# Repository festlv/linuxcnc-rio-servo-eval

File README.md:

# LinuxCNC-RIO evaluation/prototype board

This repository contains a quick&dirty board to evaluate feasibility of using [LinuxCNC-RIO](https://github.com/multigcs/LinuxCNC-RIO) for analog servo motor control.
The board is designed as an addon for [Colorlight i5](https://tomverbeure.github.io/2021/01/22/The-Colorlight-i5-as-FPGA-development-board.html) development board. 

Design contains:
* +/-10V analog output (from pwmdir input) + 24V enable output
* differential step/dir + single ended 24V enable output
* differential encoder input on DB9 connector (RS422) with index pulse. Pinout for Ditron DC10 linear scale.
* 4 single ended 24V inputs (limit switches, EStop)
* +24V input, +5V, +/- 15V outputs for development board and analog output.

__N.B.__: There is no isolation present on the board, it relies on the Ethernet isolation alone!

## Current state

The design is not verified in real hardware yet, proceed with caution. Some aspects of the design were simulated in LTSpice, see `ltspice/`

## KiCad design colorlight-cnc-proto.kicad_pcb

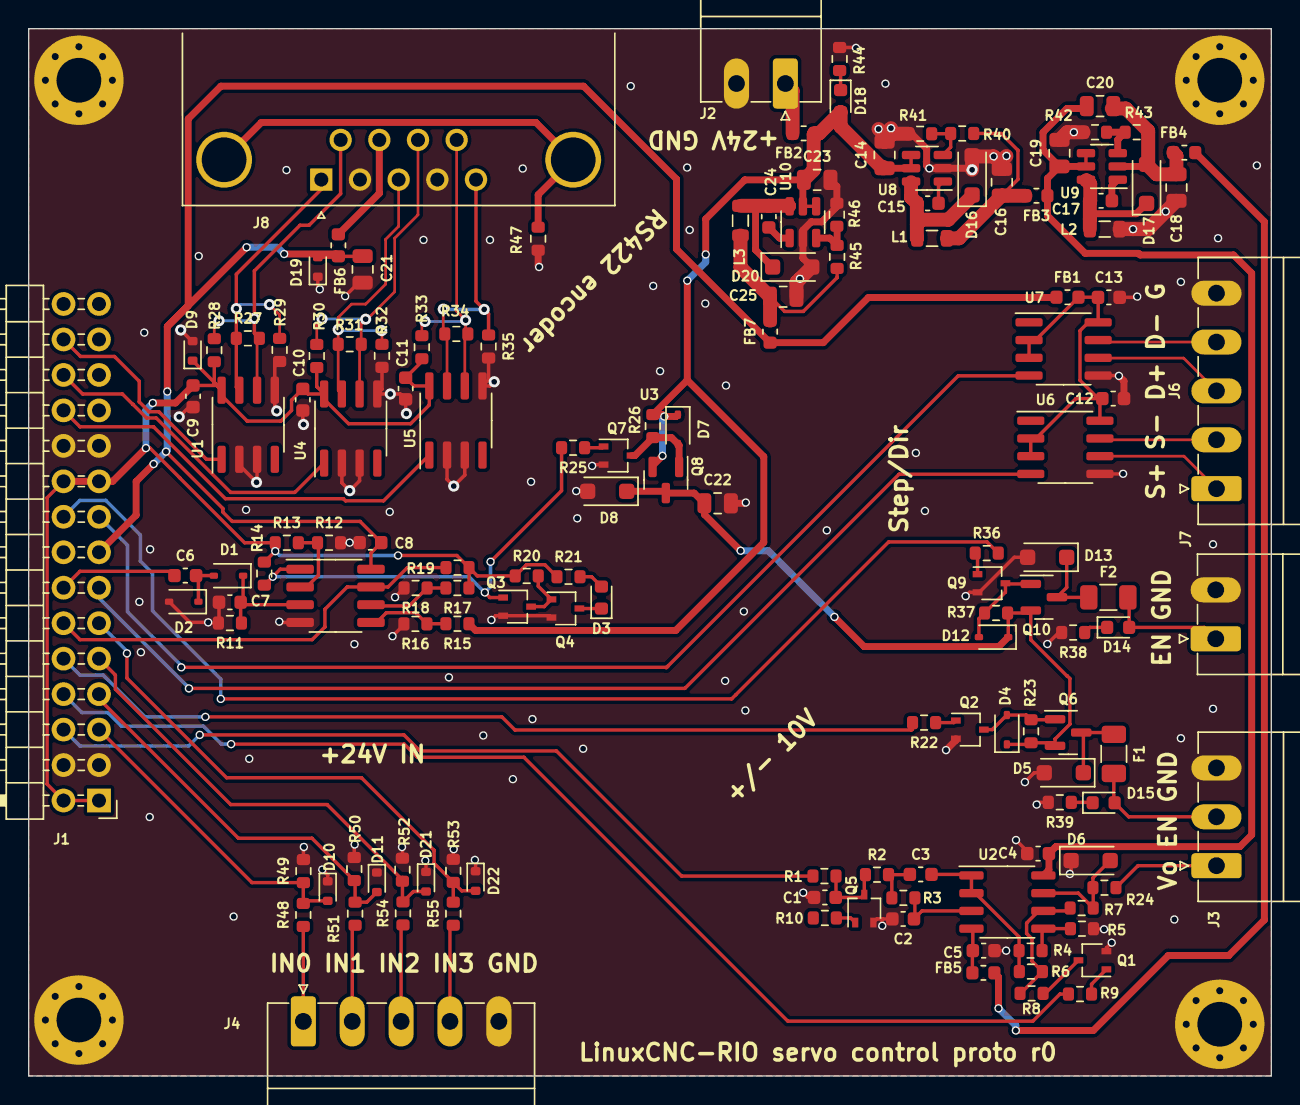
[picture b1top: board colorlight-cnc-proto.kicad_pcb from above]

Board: 2 copper layers, 89.0 x 75.0 mm, 145 parts (0 on the bottom side), 86 nets.

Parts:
C1: 3.3nF; C_0603_1608Metric
C2: 220pF; C_0603_1608Metric
C3: 680pF; C_0603_1608Metric
C4, C5, C6, C8, C9, C10, C11, C12, C13, C15, C17, C24: 0.1uF; C_0603_1608Metric
C7: 1uF; C_0603_1608Metric
C14, C16, C18, C19, C20, C21, C22, C23, C25: 10uF; C_0805_2012Metric
D1, D2: BAT54WS; D_SOD-323
D3, D14, D15: LED_RED; LED_0603_1608Metric
D4, D7, D12: BZT52C10S; D_SOD-323
D5, D8, D13: SMF24A; D_SOD-123F
D6: SMF10CA; D_SOD-123F
D9, D10, D11, D21, D22: BSD5C031V; D_SOD-523
D16, D17, D20: DSS34; D_SOD-123F
D18: LED_GREEN; LED_0603_1608Metric
D19: PESD5V0S1BBN; D_SOD-523
F1, F2: BSMD1206-100-24V; Fuse_1206_3216Metric
FB1, FB2, FB3, FB4, FB5, FB6, FB7: FB_100R_3A; L_0603_1608Metric
H1, H2, H3, H4: MH_3.2mm; MountingHole_3.2mm_M3_Pad_Via
J1: Conn_02x15_Odd_Even; PinHeader_2x15_P2.54mm_Horizontal
J2, J7: TERM-BLK-2H; PhoenixContact_MC_1,5_2-G-3.5_1x02_P3.50mm_Horizontal
J3: TERM-BLK-3H; PhoenixContact_MC_1,5_3-G-3.5_1x03_P3.50mm_Horizontal
J4, J6: TERM-BLK-5H; PhoenixContact_MC_1,5_5-G-3.5_1x05_P3.50mm_Horizontal
J8: DB9_Receptacle; DSUB-9_Female_Horizontal_P2.77x2.84mm_EdgePinOffset7.70mm_H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
L1, L2, L3: MLP2012S4R7MT0S1; L_0805_2012Metric
Q1, Q2, Q3, Q4, Q5, Q7, Q9: BSS138W; SOT-323_SC-70
Q6, Q8, Q10: AO3401A; SOT-23
R1, R4, R5, R6, R9, R10, R14, R15, R17, R18, R19, R20, R22, R23, R25, R26, R36, R37, R38, R39, R44, R48, R49, R50, R51, R52, R53, R54, R55: 10K; R_0603_1608Metric
R2: 150K; R_0603_1608Metric
R3, R11, R13: 47K; R_0603_1608Metric
R7: 70K; R_0603_1608Metric
R8: 5.83K; R_0603_1608Metric
R12: 100K; R_0603_1608Metric
R16, R21, R28, R29, R30, R32, R33, R35: 1K; R_0603_1608Metric
R24: 10R; R_0603_1608Metric
R27, R31, R34: 120R; R_0603_1608Metric
R40, R42: 510K; R_0603_1608Metric
R41, R43: 30K; R_0603_1608Metric
R45: 82K; R_0603_1608Metric
R46: 16K; R_0603_1608Metric
R47: 0R; R_0603_1608Metric
U1, U4, U5, U6, U7: CS48505S; SOIC-8_3.9x4.9mm_P1.27mm
U2: LM358DT; SO-8_3.9x4.9mm_P1.27mm
U3: LM2903; SOP-8_3.76x4.96mm_P1.27mm
U8, U9, U10: LGS5145; SOT-23-6

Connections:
+3V3: C9.1, C10.1, C11.1, D9.1 (A1), J1.1, J1.2, J1.19, J1.20, R13.1, R14.1, R17.1, R19.1, R20.1, R21.1, R28.1, R30.1, R33.1, U1.8 (VCC), U4.8 (VCC), U5.8 (VCC)
+5V: C8.1, C21.1, D19.2 (A2), FB1.1, FB6.1, FB7.1, J1.15, U3.8 (V+)
+15V: C4.1, C19.1, C20.1, FB3.1, U2.8 (V+), U9.4 (EN), U9.5 (IN)
+24V: C14.1, C23.1, D7.1 (K), D18.2 (A), FB2.2, Q8.2 (S), R15.1, R26.1, U8.4 (EN), U8.5 (IN), U10.4 (EN), U10.5 (IN)
+24V_WD: C22.1, D4.1 (K), D8.1 (A1), D12.1 (K), Q6.2 (S), Q8.3 (D), Q10.2 (S), R23.1, R37.1
-15V: FB4.2, FB5.2
/Analog output/DIR_IN: J1.8, R9.2
/Analog output/EN: J1.10, R22.2
/Analog output/EN_OUT: D15.2 (A), F1.2, J3.2
/Analog output/OUT: J3.1, R24.2
/Analog output/PWM_IN: J1.6, R1.1
/IO/INP0: D10.2 (A2), J1.5, R48.2, R49.1
/IO/INP1: D11.2 (A2), J1.7, R50.1, R51.2
/IO/INP2: D21.2 (A2), J1.9, R52.1, R54.2
/IO/INP3: D22.2 (A2), J1.11, R53.1, R55.2
/Quad encoder/A: J1.28, U1.1 (RO)
/Quad encoder/A_IN_N: J8.1, R27.1, R29.1, U1.7 (B)
/Quad encoder/A_IN_P: J8.6, R27.2, R28.2, U1.6 (A)
/Quad encoder/B: J1.26, U4.1 (RO)
/Quad encoder/B_IN_N: J8.3, R31.2, R32.1, U4.7 (B)
/Quad encoder/B_IN_P: J8.8, R30.2, R31.1, U4.6 (A)
/Quad encoder/Z: J1.24, U5.1 (RO)
/Quad encoder/Z_IN_N: J8.5, R34.2, R35.1, U5.7 (B)
/Quad encoder/Z_IN_P: J8.9, R33.2, R34.1, U5.6 (A)
/SD_EN: J1.18, R36.2
/Step Dir/DIR: J1.17, U7.4 (DI)
/Step Dir/DIR_OUT_N: J6.4, U7.7 (B)
/Step Dir/DIR_OUT_P: J6.3, U7.6 (A)
/Step Dir/EN_OUT: D14.2 (A), F2.2, J7.1
/Step Dir/STEP: J1.13, U6.4 (DI)
/Step Dir/STEP_OUT_N: J6.2, U6.7 (B)
/Step Dir/STEP_OUT_P: J6.1, U6.6 (A)
/Watchdog/24V_OK: J1.12, R19.2, U3.7
/Watchdog/PWM_IN: C6.1, J1.14
GND: C1.2, C2.2, C4.2, C5.2, C7.2, C8.2, C9.2, C10.2, C11.2, C12.2, C13.2, C14.2, C16.2, C18.1, C19.2, C21.2, C22.2, C23.2, C25.2, D2.2 (A), D5.2 (A2), D6.1 (A1), D8.2 (A2), D9.2 (A2), D10.1 (A1), D11.1 (A1), D13.2 (A2), D16.2 (A), D19.1 (A1), D20.2 (A), D21.1 (A1), D22.1 (A1), H1.1, H2.1, H3.1, H4.1, J1.3, J1.4, J1.21, J1.22, J2.2, J3.3, J4.5, J6.5, J7.2, J8.2, J8.4, L2.2, Q1.2 (S), Q2.2 (S), Q3.2 (S), Q4.2 (S), Q5.2 (S), Q7.2 (S), Q9.2 (S), R5.1, R11.2, R12.2, R16.2, R18.2, R29.2, R32.2, R35.2, R38.2, R39.2, R41.2, R42.1, R44.2, R46.2, R47.2, R49.2, R50.2, R52.2, R53.2, U1.2 (~RE), U1.3 (DE), U1.5 (GND), U3.4 (V-), U4.2 (~RE), U4.3 (DE), U4.5 (GND), U5.2 (~RE), U5.3 (DE), U5.5 (GND), U6.5 (GND), U7.5 (GND), U8.2 (GND), U10.2 (GND)
unnamed: C3.1, R2.2, R3.1
unnamed: C16.1, FB3.2, L1.2, R40.1
unnamed: C25.1, FB7.2, L3.2, R45.1
unnamed: C6.2, D1.2 (A), D2.1 (K)
unnamed: C7.1, D1.1 (K), R11.1, U3.3 (+)
unnamed: D3.2 (A), R21.2
unnamed: D3.1 (K), Q4.3 (D)
unnamed: D4.2 (A), Q2.3 (D), Q6.1 (G), R23.2
unnamed: D5.1 (A1), F1.1, Q6.3 (D)
unnamed: D6.2 (A2), R7.1, R24.1, U2.7
unnamed: D7.2 (A), Q7.3 (D), Q8.1 (G), R26.2
unnamed: D12.2 (A), Q9.3 (D), Q10.1 (G), R37.2
unnamed: D13.1 (A1), F2.1, Q10.3 (D)
unnamed: D14.1 (K), R38.1
unnamed: D15.1 (K), R39.1
unnamed: C15.2, D16.1 (K), L1.1, U8.6 (SW)
unnamed: C18.2, C20.2, D17.2 (A), FB4.1, R43.2, U9.2 (GND)
unnamed: C17.2, D17.1 (K), L2.1, U9.6 (SW)
unnamed: D18.1 (K), R44.1
unnamed: C24.2, D20.1 (K), L3.1, U10.6 (SW)
unnamed: FB6.2, J8.7
unnamed: FB2.1, J2.1
unnamed: J4.1, R48.1
unnamed: J4.2, R51.1
unnamed: J4.3, R54.1
unnamed: J4.4, R55.1
unnamed: J8.0 (PAD), R47.1
unnamed: Q1.3 (D), R8.1
unnamed: Q1.1 (G), R9.1
unnamed: Q2.1 (G), R22.1
unnamed: C1.1, Q5.3 (D), R1.2, R2.1
unnamed: Q5.1 (G), R10.1
unnamed: Q7.1 (G), R25.1
unnamed: Q9.1 (G), R36.1
unnamed: C2.1, R3.2, U2.3 (+)
unnamed: C3.2, R4.1, R6.2, U2.1, U2.2 (-)
unnamed: R4.2, R5.2, U2.5 (+)
unnamed: R6.1, R7.2, R8.2, U2.6 (-)
unnamed: C5.1, FB5.1, U2.4 (V-)
unnamed: R12.1, R13.2, U3.2 (-)
unnamed: R15.2, R16.1, U3.5 (+)
unnamed: R17.2, R18.1, U3.6 (-)
unnamed: C12.1, C13.1, FB1.2, U6.2 (~RE), U6.3 (DE), U6.8 (VCC), U7.2 (~RE), U7.3 (DE), U7.8 (VCC)
unnamed: C15.1, U8.1 (BS)
unnamed: R40.2, R41.1, U8.3 (FB)
unnamed: C17.1, U9.1 (BS)
unnamed: R42.2, R43.1, U9.3 (FB)
unnamed: C24.1, U10.1 (BS)
unnamed: R45.2, R46.1, U10.3 (FB)
WATCHDOG: Q3.1 (G), R14.2, R25.2, U3.1
WATCHDOG_INV: Q3.3 (D), Q4.1 (G), R20.2

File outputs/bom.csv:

"Source:","/home/reinis/personal/cnc/colorlight-cnc-proto/colorlight-cnc-proto.kicad_sch"
"Date:","Thu 07 Sep 2023 10:59:34 AM EEST"
"Tool:","Eeschema 7.0.7"
"Generator:","/usr/share/kicad/plugins/bom_csv_grouped_by_value.py"
"Component Count:","141"

"Collated Components:"

"Item","Qty","Reference(s)","Value","LibPart","Footprint","Datasheet","DNP","LCSC#","MPN","Manufacturer"
"1","1","C1","3.3nF","Device:C_Small","Capacitor_SMD:C_0603_1608Metric","~","","","",""
"2","1","C2","220pF","Device:C_Small","Capacitor_SMD:C_0603_1608Metric","~","","","",""
"3","1","C3","680pF","Device:C_Small","Capacitor_SMD:C_0603_1608Metric","~","","","",""
"4","12","C4, C5, C6, C8, C9, C10, C11, C12, C13, C15, C17, C24","0.1uF","Device:C_Small","Capacitor_SMD:C_0603_1608Metric","~","","","",""
"5","1","C7","1uF","Device:C_Small","Capacitor_SMD:C_0603_1608Metric","~","","","",""
"6","9","C14, C16, C18, C19, C20, C21, C22, C23, C25","10uF","Device:C_Small","Capacitor_SMD:C_0805_2012Metric","~","","C440198","GRM21BR61H106KE43L",""
"7","2","D1, D2","BAT54WS","hadv-diodes:BAT54WS","Diode_SMD:D_SOD-323","https://datasheet.lcsc.com/lcsc/2206271801_FUXINSEMI-BAT54WS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","","C3040452","BAT54WS","Fuxinsemi"
"8","3","D3, D14, D15","LED_RED","hadv-ui:LED_RED","LED_SMD:LED_0603_1608Metric","~","","C434419","SZYY0603R","Yongyu Photoelectric"
"9","3","D4, D7, D12","BZT52C10S","hadv-diodes:BZT52C10S","Diode_SMD:D_SOD-323","~","","C5270769","BZT52C10S","YFW"
"10","3","D5, D8, D13","SMF24A","hadv-protection:SMF24A","Diode_SMD:D_SOD-123F","https://datasheet.lcsc.com/lcsc/2304140030_Shandong-Jingdao-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","","C169430","SMF24A","Shandong Jingdao Microelectronics"
"11","1","D6","SMF10CA","hadv-protection:SMF10CA","Diode_SMD:D_SOD-123F","https://www.littelfuse.com/~/media/electronics/datasheets/tv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","","C5310922","SMF10CA","Sunmate"
"12","5","D9, D10, D11, D21, D22","BSD5C031V","hadv-protection:BSD5C031V","Diode_SMD:D_SOD-523","https://datasheet.lcsc.com/lcsc/1912111437_BORN-BSD5C031V_C1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","","C151984","BSD5C031V","BORN"
"13","3","D16, D17, D20","DSS34","hadv-diodes:DSS34","Diode_SMD:D_SOD-123F","https://datasheet.lcsc.com/lcsc/2004141809_BORN-DSS34_C511866.pdf","","C511866","DSS34","BORN"
"14","1","D18","LED_GREEN","hadv-ui:LED_GREEN","LED_SMD:LED_0603_1608Metric","~","","C434423","SZYY0603YG","Yongyu Photoelectric"
"15","1","D19","PESD5V0S1BBN","hadv-protection:PESD5V0S1BBN","Diode_SMD:D_SOD-523","https://datasheet.lcsc.com/lcsc/1912111437_BORN-PESD5V0S1BBN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","","C314264","PESD5V0S1BBN","BORN"
"16","2","F1, F2","BSMD1206-100-24V","hadv-protection:BSMD1206-100-24V","Fuse:Fuse_1206_3216Metric","~","","C910830","BSMD1206-100-24V","BHFUSE"
"17","7","FB1, FB2, FB3, FB4, FB5, FB6, FB7","FB_100R_3A","hadv-passives:FB_100R_3A","Inductor_SMD:L_0603_1608Metric","~","","C96995","UPZ1608E101-3R0TF","Sunlord"
"18","1","J1","Conn_02x15_Odd_Even","Connector_Generic:Conn_02x15_Odd_Even","Connector_PinHeader_2.54mm:PinHeader_2x15_P2.54mm_Horizontal","~","","C2894995","",""
"19","2","J2, J7","TERM-BLK-2H","hadv-connectors:TERM-BLK-2H","Connector_Phoenix_MC:PhoenixContact_MC_1,5_2-G-3.5_1x02_P3.50mm_Horizontal","~","","C441171","KF2EDGR-3.5-2P","Cixi Kefa Elec"
"20","1","J3","TERM-BLK-3H","hadv-connectors:TERM-BLK-3H","Connector_Phoenix_MC:PhoenixContact_MC_1,5_3-G-3.5_1x03_P3.50mm_Horizontal","~","","C441172","KF2EDGR-3.5-3P","Cixi Kefa Elec"
"21","2","J4, J6","TERM-BLK-5H","hadv-connectors:TERM-BLK-5H","Connector_Phoenix_MC:PhoenixContact_MC_1,5_5-G-3.5_1x05_P3.50mm_Horizontal","~","","C441174","KF2EDGR-3.5-5P","Cixi Kefa Elec"
"22","1","J8","DB9_Receptacle","hadv-connectors:DB9_Receptacle","Connector_Dsub:DSUB-9_Female_Horizontal_P2.77x2.84mm_EdgePinOffset7.70mm_Housed_MountingHolesOffset9.12mm"," ~","","C141882","D-DMR009PF-D002","Ckmtw"
"23","3","L1, L2, L3","MLP2012S4R7MT0S1","hadv-inductors:MLP2012S4R7MT0S1","Inductor_SMD:L_0805_2012Metric","~","","C87543","MLP2012S4R7MT0S1","TDK"
"24","7","Q1, Q2, Q3, Q4, Q5, Q7, Q9","BSS138W","hadv-transistors:BSS138W","Package_TO_SOT_SMD:SOT-323_SC-70","~","","C504052","BSS138W","Jiangsu Changjing Electronics Technology Co., Ltd."
"25","3","Q6, Q8, Q10","AO3401A","hadv-transistors:AO3401A","Package_TO_SOT_SMD:SOT-23","http://www.vishay.com/docs/70209/70209.pdf","","C347476","AO3401A","UMW"
"26","29","R1, R4, R5, R6, R9, R10, R14, R15, R17, R18, R19, R20, R22, R23, R25, R26, R36, R37, R38, R39, R44, R48, R49, R50, R51, R52, R53, R54, R55","10K","Device:R_Small","Resistor_SMD:R_0603_1608Metric","~","","","",""
"27","1","R2","150K","Device:R_Small","Resistor_SMD:R_0603_1608Metric","~","","","",""
"28","3","R3, R11, R13","47K","Device:R_Small","Resistor_SMD:R_0603_1608Metric","~","","","",""
"29","1","R7","70K","Device:R_Small","Resistor_SMD:R_0603_1608Metric","~","","","",""
"30","1","R8","5.83K","Device:R_Small","Resistor_SMD:R_0603_1608Metric","~","","","",""
"31","1","R12","100K","Device:R_Small","Resistor_SMD:R_0603_1608Metric","~","","","",""
"32","8","R16, R21, R28, R29, R30, R32, R33, R35","1K","Device:R_Small","Resistor_SMD:R_0603_1608Metric","~","","","",""
"33","1","R24","10R","Device:R_Small","Resistor_SMD:R_0603_1608Metric","~","","","",""
"34","3","R27, R31, R34","120R","Device:R_Small","Resistor_SMD:R_0603_1608Metric","~","","","",""
"35","2","R40, R42","510K","Device:R_Small","Resistor_SMD:R_0603_1608Metric","~","","","",""
"36","2","R41, R43","30K","Device:R_Small","Resistor_SMD:R_0603_1608Metric","~","","","",""
"37","1","R45","82K","Device:R_Small","Resistor_SMD:R_0603_1608Metric","~","","","",""
"38","1","R46","16K","Device:R_Small","Resistor_SMD:R_0603_1608Metric","~","","","",""
"39","1","R47","0R","Device:R_Small","Resistor_SMD:R_0603_1608Metric","~","","","",""
"40","5","U1, U4, U5, U6, U7","CS48505S","hadv-interface:CS48505S","Package_SO:SOIC-8_3.9x4.9mm_P1.27mm","https://datasheet.lcsc.com/lcsc/2207041730_Chipanalog-CS4850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","","C3202824","CS48505S","Chipanalog"
"41","1","U2","LM358DT","hadv-opamps:LM358DT","Package_SO:SO-8_3.9x4.9mm_P1.27mm","http://www.ti.com/lit/ds/symlink/lm2904-n.pdf","","C9418","LM358DT","STMicroelectronics"
"42","1","U3","LM2903","hadv-opamps:LM393","Package_SO:SOP-8_3.76x4.96mm_P1.27mm","http://www.ti.com/lit/ds/symlink/lm393.pdf","","C400839","LM393","IDCHIP"
"43","3","U8, U9, U10","LGS5145","hadv-vregs:LGS5145","Package_TO_SOT_SMD:SOT-23-6","https://datasheet.lcsc.com/lcsc/2304071600_Legend-Si-LGS5145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","","C5123971","LGS5145",""

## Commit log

2023-09-07 Initial commit, r0 PCB order
